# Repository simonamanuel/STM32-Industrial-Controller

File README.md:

# STM32 Industrial Sensor, DAQ & Actuator Controller

**Status: CAD-stage portfolio design (Revision D). Not fabricated, physically tested, or approved for industrial deployment.**

This repository contains an electronic design project built around an STM32F103C8T6 microcontroller, with a four-layer KiCad PCB, mixed-signal sensing, low-voltage power conversion, wired communications, and two switched DC actuator channels. It showcases design-file organization, schematic/PCB review, bill-of-materials management, and documented limitations.

## PCB Design Gallery

### PCB Layout

### 3D PCB View

### Front Copper Routing

### Electrical Schematic
[View Schematic PDF](KiCad/STM32_Industrial_Controller.pdf)

## At a glance

| Aspect | Revision D design target / supplied evidence |
| --- | --- |
| PCB | 4 layers, 218 × 146 mm, 1.6 mm FR-4 (per fabrication notes) |
| Controller | STM32F103C8T6, 3.3 V logic |
| Input | 9–30 V DC for logic; actuator supply specified separately as 9–18 V, nominal 12 V |
| Power rails | 5 V buck regulator, 3.3 V LDO |
| Analog sensing | Two nominal 0–10 V inputs with scaling/filtering to MCU ADC range |
| Interfaces | I²C, SPI, UART, SWD, half-duplex RS-485 |
| Actuators | Two nominal 1.5 A low-side switched channels (design target, not measured) |
| Schematic ERC | **0 errors / 0 warnings** in supplied Revision D report; four ERC check categories ignored |
| PCB DRC | **0 reported violations; 0 unconnected pads; 0 footprint errors**, none ignored in supplied report |
| Firmware | Not included in this Revision D archive; no firmware build or tests claimed |
| Physical verification | **Not performed** |

## System overview

```mermaid
flowchart TD
  A[External DC supply] --> B[Fuse + input protection]
  B --> C[Protected DC distribution]
  C --> D[5 V buck regulator]
  D --> E[3.3 V LDO]
  E --> F[STM32F103C8T6]
  G[Two analog sensor inputs] --> F
  F <--> H[I2C / SPI / UART / SWD]
  F <--> I[RS-485 transceiver]
  C --> J[Two fused actuator supplies]
  F --> K[Two MOSFET low-side switches]
  J --> K
```

The block diagram summarizes intended functions; it does not replace the authoritative schematic or prove electrical performance.

## Repository layout

- [`KiCad/`](KiCad/) — editable KiCad 10 schematic and four-layer PCB, project settings and local footprints.
- [`Manufacturing/`](Manufacturing/) — existing design-stage Gerbers, drills, BOM, placement outputs, ERC/DRC reports, and fabrication notes. **Not approved for production or ordering.**
- [`Documentation/DESIGN_SUMMARY.md`](Documentation/DESIGN_SUMMARY.md) — architecture and design assumptions.
- [`Documentation/VERIFICATION_STATUS.md`](Documentation/VERIFICATION_STATUS.md) — what has and has not been validated.
- [`Documentation/OPEN_DESIGN_ITEMS.md`](Documentation/OPEN_DESIGN_ITEMS.md) — unresolved concerns and disclosure statements.
- [`Documentation/PORTFOLIO_PRESENTATION.md`](Documentation/PORTFOLIO_PRESENTATION.md) — engineering scope, design deliverables, and verification status.
- [`Documentation/FINISHING_CHECKLIST.md`](Documentation/FINISHING_CHECKLIST.md) — minimal remaining steps for a CAD-only portfolio.
- [`Documentation/Original_Revision_D_README.md`](Documentation/Original_Revision_D_README.md) — README supplied with original Revision D archive, preserved unchanged.

## Opening the project

1. Open `KiCad/STM32_Industrial_Controller.kicad_pro` in KiCad 10 on macOS.
2. Open the `.kicad_sch` schematic and `.kicad_pcb` board.
3. Run **Inspect → Electrical Rules Checker** in Schematic Editor.
4. Run **Inspect → Design Rules Checker** in PCB Editor, enabling zone refill and schematic-parity checking.
5. Capture schematic, copper-layer, and KiCad 3D Viewer screenshots for the portfolio; see the finishing checklist.

## Engineering status and limitations

The **provided** ERC and DRC reports show clean CAD rule checks. Those checks do not establish functional electrical correctness, actual thermal performance, component suitability, assembly fit, or field reliability. An independent KiCad rerun was not performed during preparation of these portfolio documents.

**Known unresolved review item:** the design directly drives `IRLML0060` MOSFET gates from approximately 3.3 V MCU logic. Their guaranteed on-resistance is not specified at that exact gate voltage in the previously reviewed datasheet. The 1.5 A actuator performance at 3.3 V gate drive is therefore **not claimed as verified**. A separate gate-driver integration was proposed but was **not incorporated into this Revision D baseline**. Additional footprint/mechanical and continuous-current/thermal reviews remain open; see [`OPEN_DESIGN_ITEMS.md`](Documentation/OPEN_DESIGN_ITEMS.md).

**This design is not a safety controller, not a certified industrial product, and not a physical prototype.**

## Project objectives

This project explores the design and integration of embedded control hardware, mixed-signal sensor interfaces, industrial communication protocols, protected power distribution, and actuator-control circuitry.

Future development will focus on resolving outstanding electrical design considerations, PCB fabrication, hardware bring-up, embedded firmware development, and experimental performance verification.

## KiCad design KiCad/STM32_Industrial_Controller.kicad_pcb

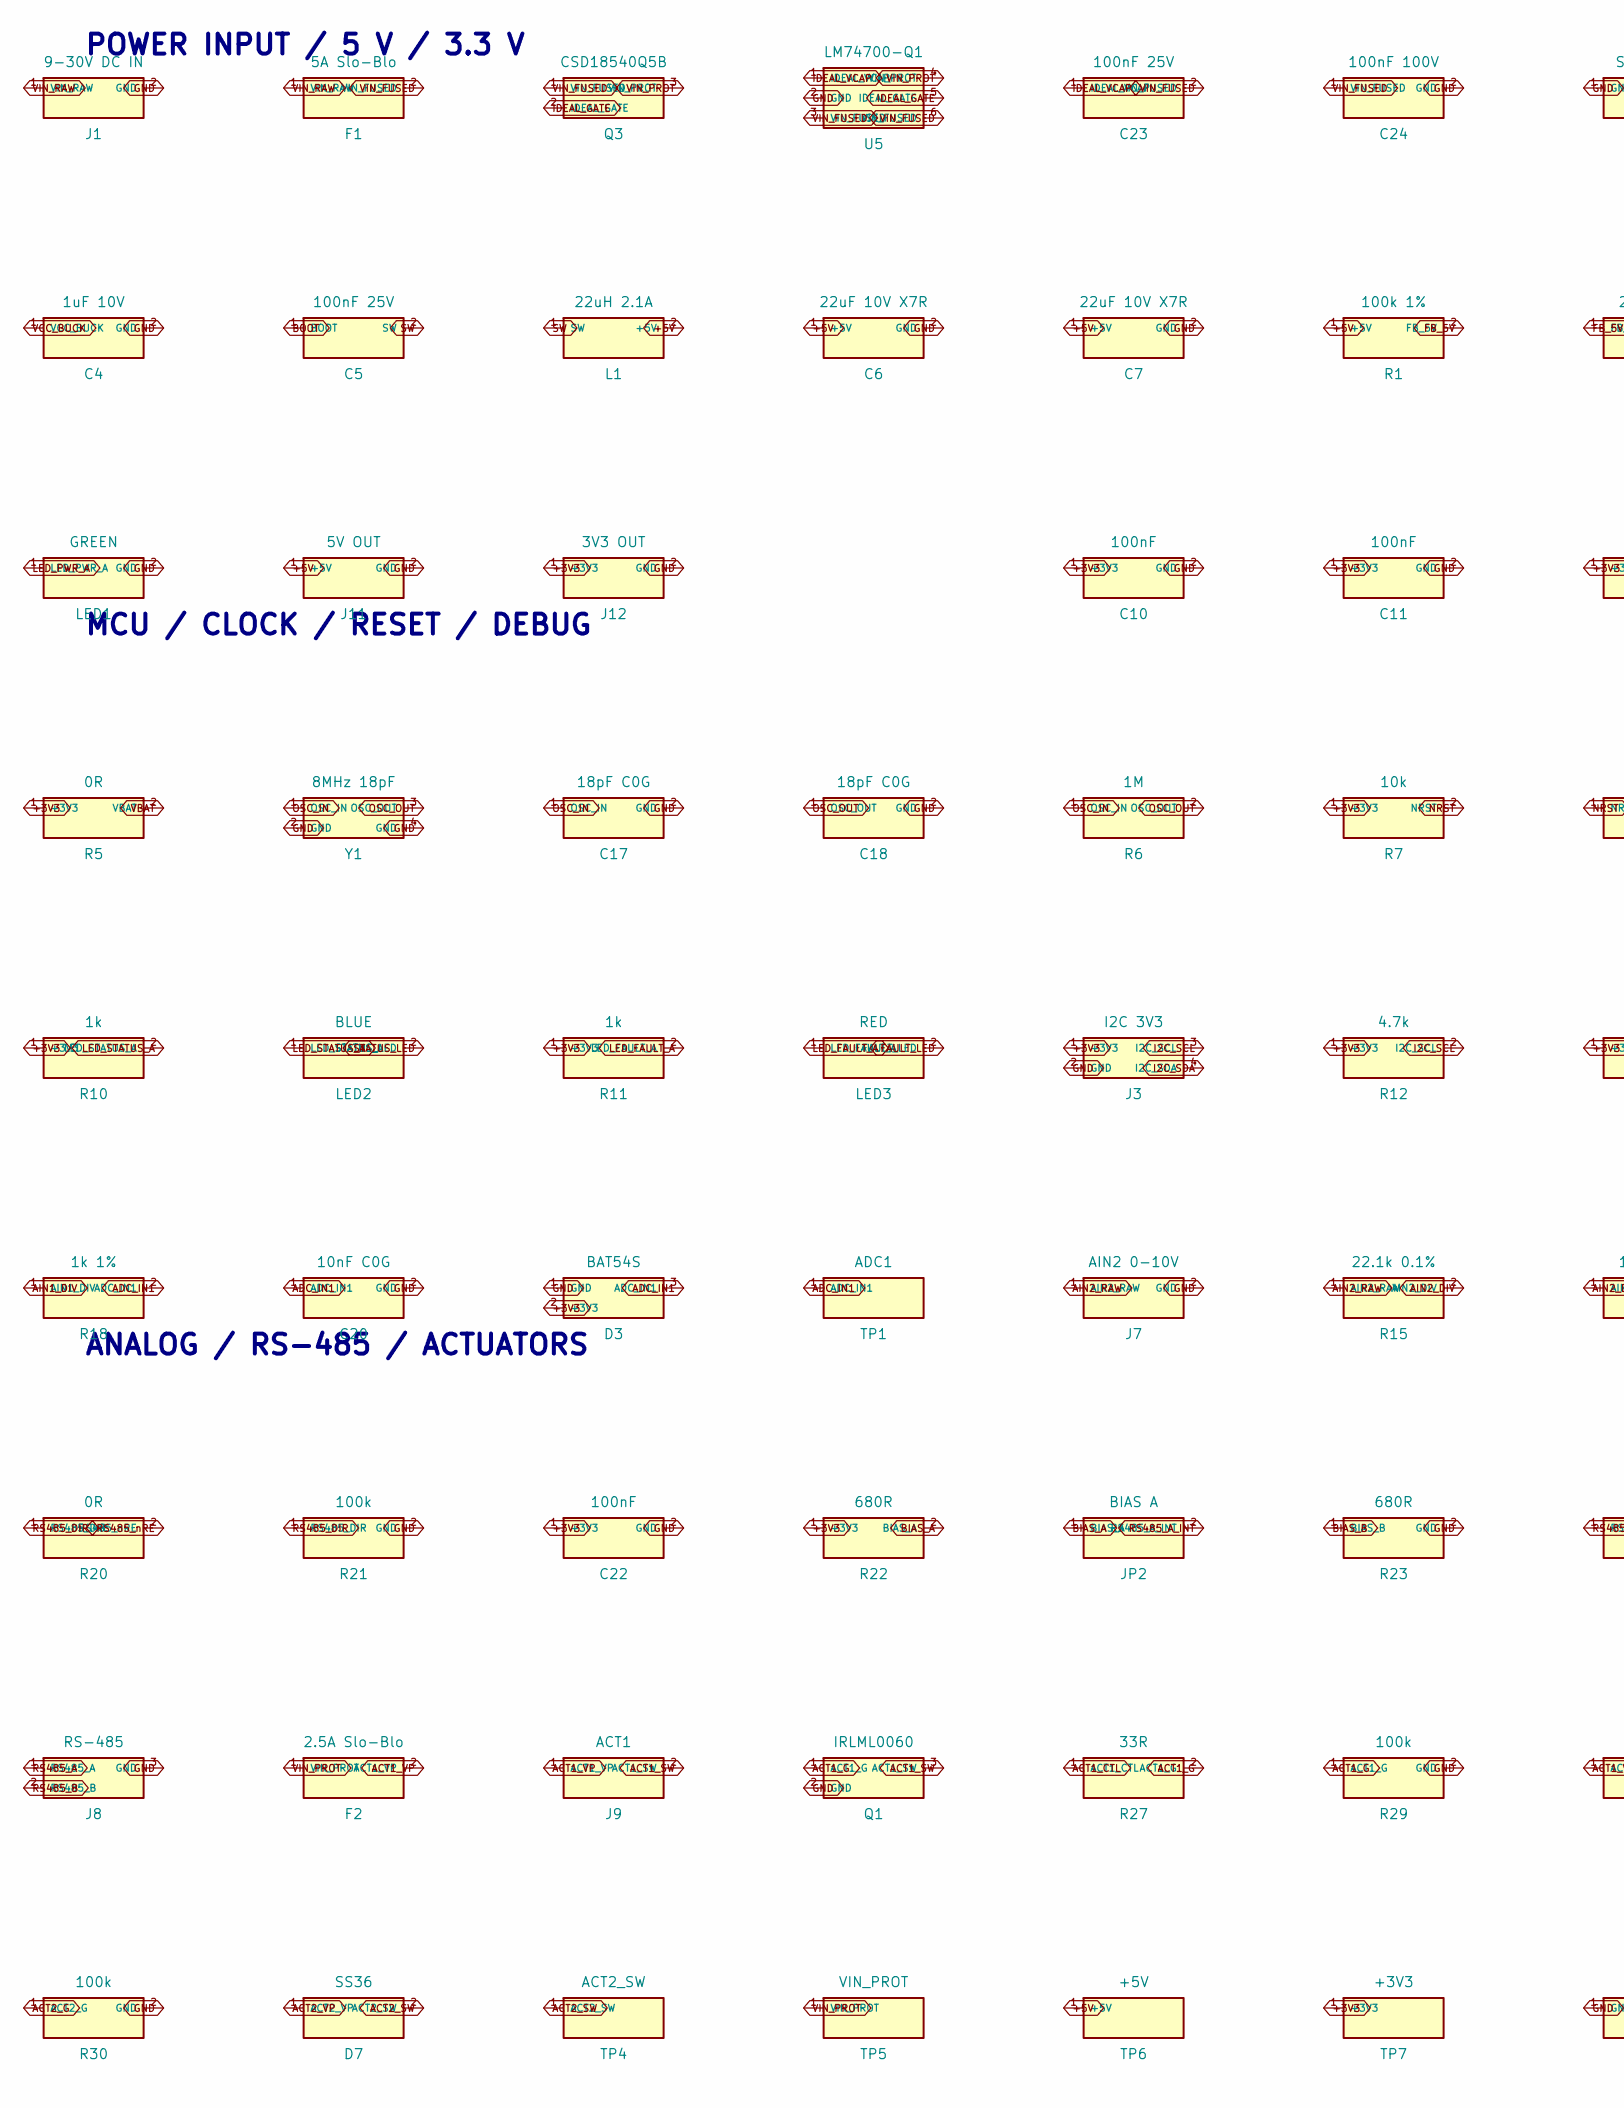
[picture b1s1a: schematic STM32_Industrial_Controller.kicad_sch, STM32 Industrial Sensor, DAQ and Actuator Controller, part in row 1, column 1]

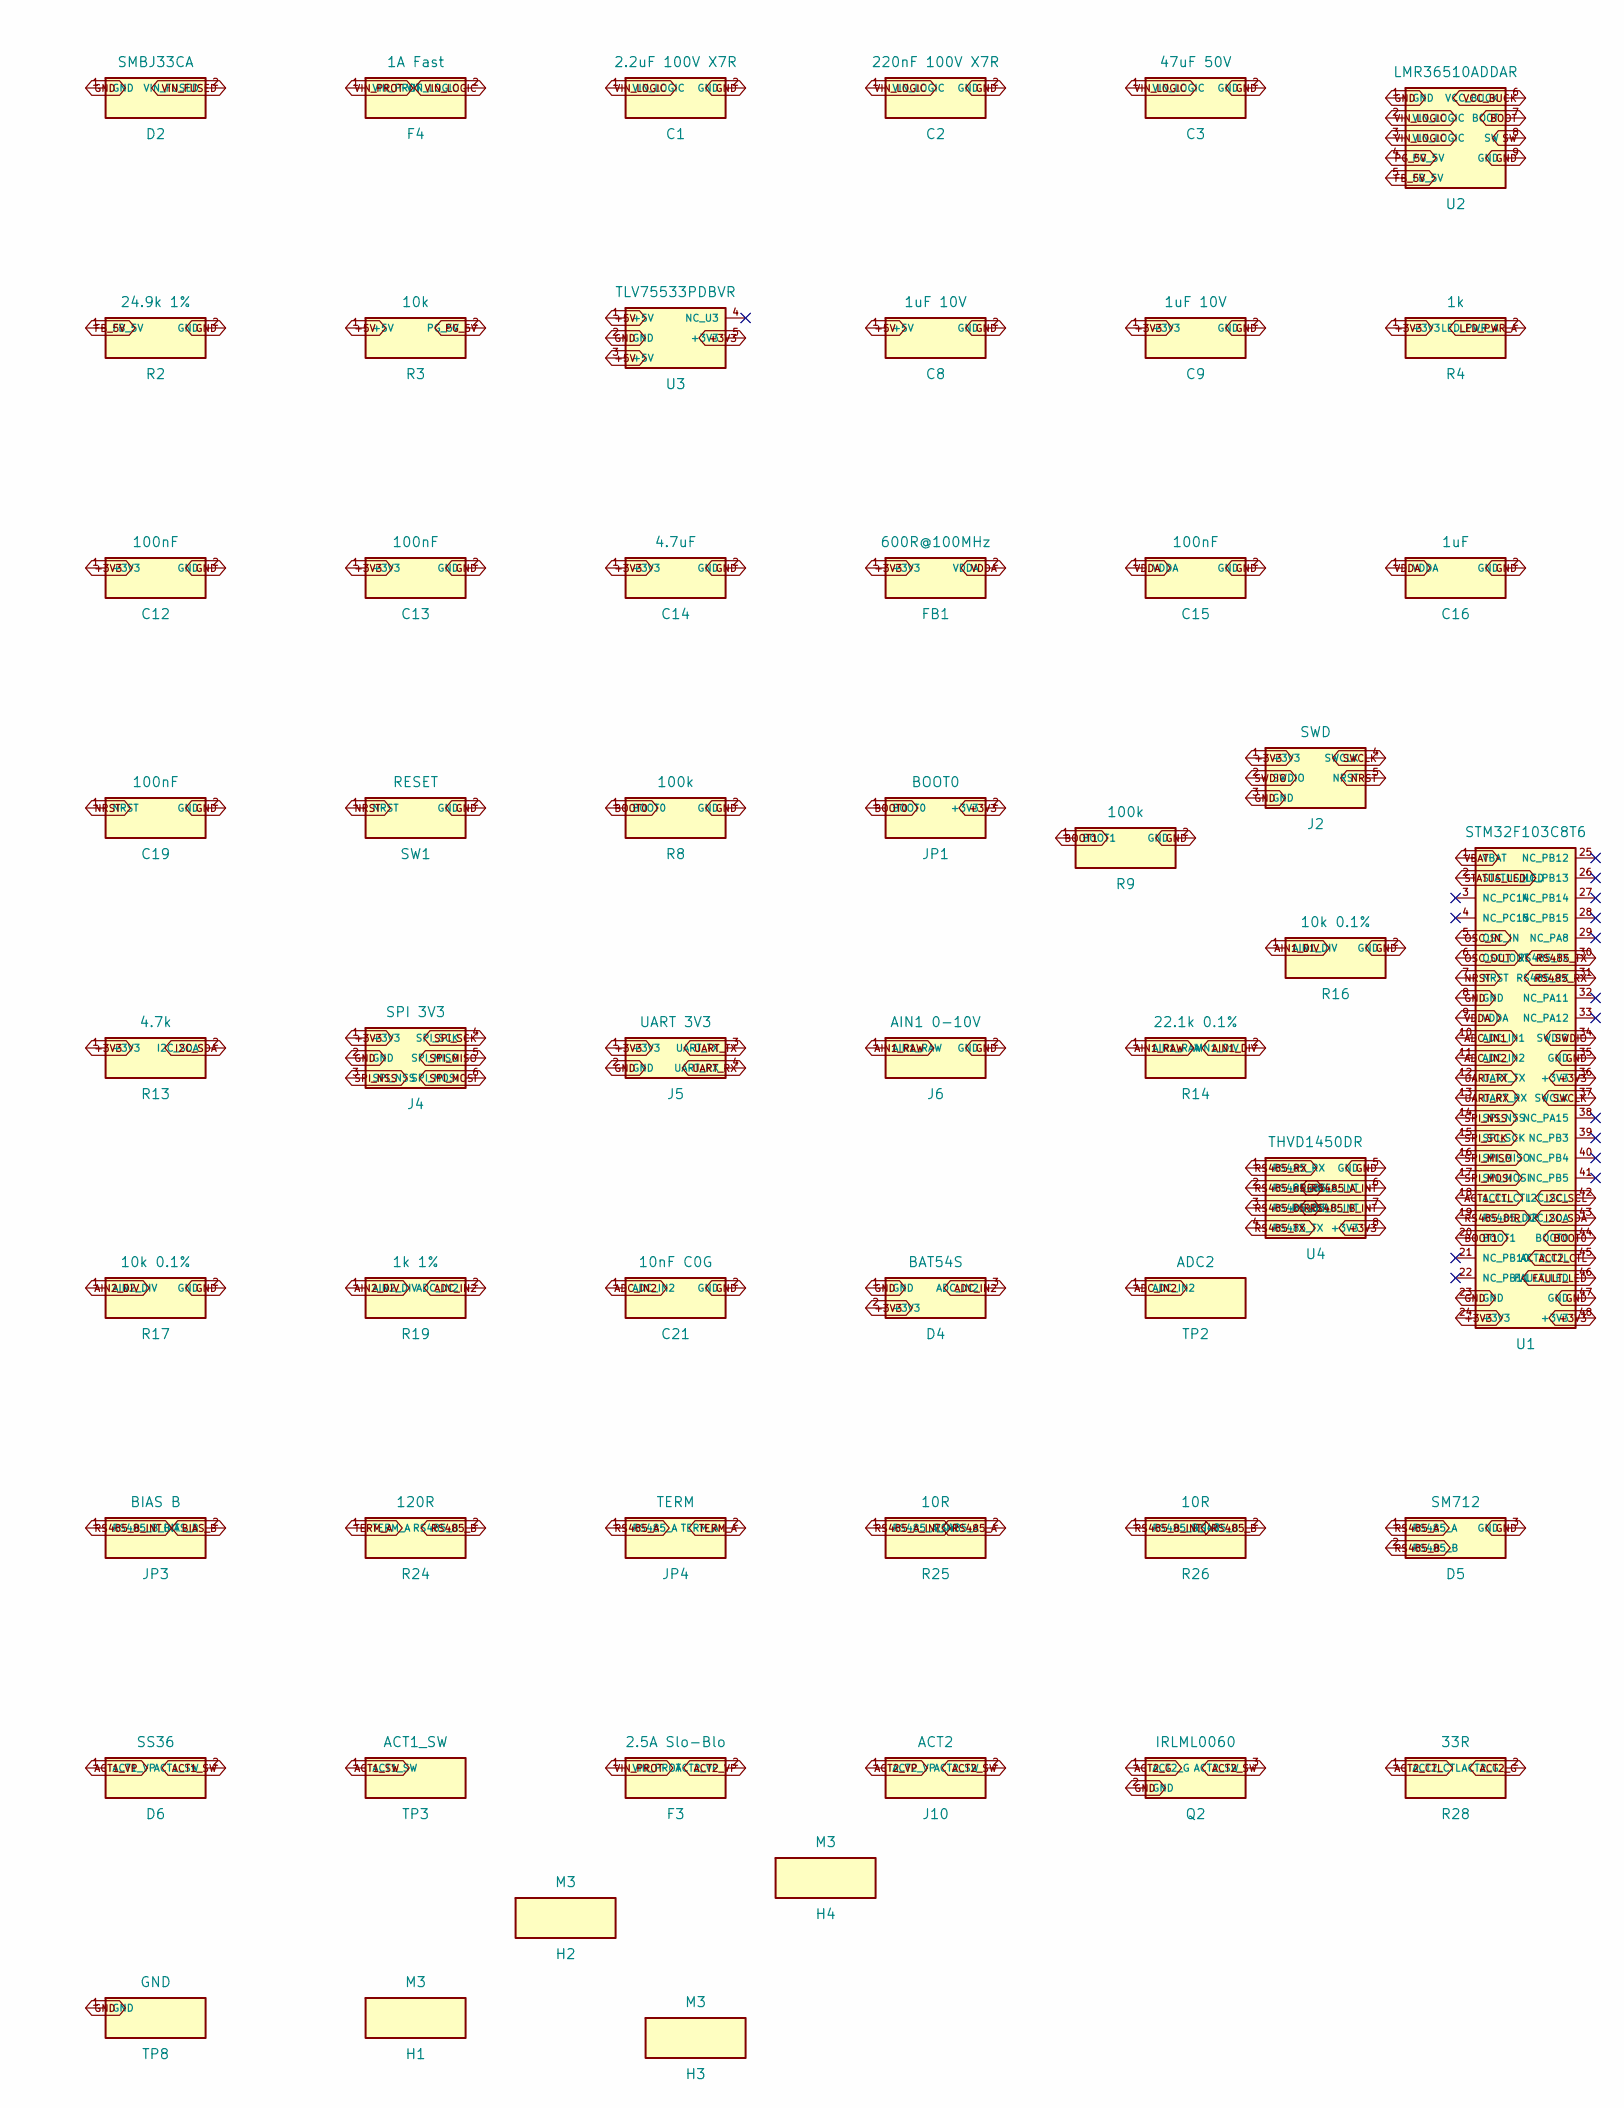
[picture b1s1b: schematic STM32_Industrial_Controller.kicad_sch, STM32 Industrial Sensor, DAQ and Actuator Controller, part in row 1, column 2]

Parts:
C1: 2.2uF 100V X7R; C1210
C2: 220nF 100V X7R; C0603
C3: 47uF 50V; CAP_SMD_63
C4, C8, C9: 1uF 10V; C0603
C5, C23: 100nF 25V; C0603
C6, C7: 22uF 10V X7R; C1210
C10, C11, C12, C13, C15, C19, C22: 100nF; C0603
C14: 4.7uF; C0603
C16: 1uF; C0603
C17, C18: 18pF C0G; C0603
C20, C21: 10nF C0G; C0603
C24: 100nF 100V; C0603
D2: SMBJ33CA; SMB
D3, D4: BAT54S; SOT23
D5: SM712; SOT23
D6, D7: SS36; SMA_K_RIGHT
F1: 5A Slo-Blo; FUSE_NANO2
F2, F3: 2.5A Slo-Blo; FUSE_NANO2
F4: 1A Fast; FUSE_NANO2
FB1: 600R@100MHz; R0603
H1, H2, H3, H4: M3; MOUNT
J1: 9-30V DC IN; TERM2
J2: SWD; HDR5
J3: I2C 3V3; HDR4
J4: SPI 3V3; HDR6
J5: UART 3V3; HDR4
J6: AIN1 0-10V; TERM2
J7: AIN2 0-10V; TERM2
J8: RS-485; TERM3
J9: ACT1; TERM2
J10: ACT2; TERM2
J11: 5V OUT; HDR2
J12: 3V3 OUT; HDR2
JP1: BOOT0; HDR2
JP2: BIAS A; HDR2
JP3: BIAS B; HDR2
JP4: TERM; HDR2
L1: 22uH 2.1A; IND_6X6
LED1: GREEN; LED0603
LED2: BLUE; LED0603
LED3: RED; LED0603
Q1, Q2: IRLML0060; SOT23
Q3: CSD18540Q5B; SON5X6_8
R1: 100k 1%; R0603
R2: 24.9k 1%; R0603
R3, R7: 10k; R0603
R4, R10, R11: 1k; R0603
R5, R20: 0R; R0603
R6: 1M; R0603
R8, R9, R21, R29, R30: 100k; R0603
R12, R13: 4.7k; R0603
R14, R15: 22.1k 0.1%; R0603
R16, R17: 10k 0.1%; R0603
R18, R19: 1k 1%; R0603
R22, R23: 680R; R0603
R24: 120R; R0603
R25, R26: 10R; R0603
R27, R28: 33R; R0603
SW1: RESET; BUTTON
TP1: ADC1; TP
TP2: ADC2; TP
TP3: ACT1_SW; TP
TP4: ACT2_SW; TP
TP5: VIN_PROT; TP
TP6: +5V; TP
TP7: +3V3; TP
TP8: GND; TP
U1: STM32F103C8T6; LQFP48
U2: LMR36510ADDAR; HSOIC8_EP
U3: TLV75533PDBVR; SOT23_5
U4: THVD1450DR; SOIC8
U5: LM74700-Q1; SOT23_6
Y1: 8MHz 18pF; XTAL4

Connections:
+3V3: C9.1 (+3V3), C10.1 (+3V3), C11.1 (+3V3), C12.1 (+3V3), C13.1 (+3V3), C14.1 (+3V3), C22.1 (+3V3), D3.2 (+3V3), D4.2 (+3V3), FB1.1 (+3V3), J2.1 (+3V3), J3.1 (+3V3), J4.1 (+3V3), J5.1 (+3V3), J12.1 (+3V3), JP1.2 (+3V3), R4.1 (+3V3), R5.1 (+3V3), R7.1 (+3V3), R10.1 (+3V3), R11.1 (+3V3), R12.1 (+3V3), R13.1 (+3V3), R22.1 (+3V3), TP7.1, U1.24 (+3V3), U1.36 (+3V3), U1.48 (+3V3), U3.5 (+3V3), U4.8 (+3V3)
+5V: C6.1 (+5V), C7.1 (+5V), C8.1 (+5V), J11.1 (+5V), L1.2 (+5V), R1.1 (+5V), R3.1 (+5V), TP6.1, U3.1 (+5V), U3.3 (+5V)
ACT1_CTL: R27.1 (ACT1_CTL), U1.18 (ACT1_CTL)
ACT1_G: Q1.1 (ACT1_G), R27.2 (ACT1_G), R29.1 (ACT1_G)
ACT1_SW: D6.2 (ACT1_SW), J9.2 (ACT1_SW), Q1.3 (ACT1_SW), TP3.1
ACT1_VP: D6.1 (ACT1_VP), F2.2 (ACT1_VP), J9.1 (ACT1_VP)
ACT2_CTL: R28.1 (ACT2_CTL), U1.45 (ACT2_CTL)
ACT2_G: Q2.1 (ACT2_G), R28.2 (ACT2_G), R30.1 (ACT2_G)
ACT2_SW: D7.2 (ACT2_SW), J10.2 (ACT2_SW), Q2.3 (ACT2_SW), TP4.1
ACT2_VP: D7.1 (ACT2_VP), F3.2 (ACT2_VP), J10.1 (ACT2_VP)
ADC_IN1: C20.1 (ADC_IN1), D3.3 (ADC_IN1), R18.2 (ADC_IN1), TP1.1, U1.10 (ADC_IN1)
ADC_IN2: C21.1 (ADC_IN2), D4.3 (ADC_IN2), R19.2 (ADC_IN2), TP2.1, U1.11 (ADC_IN2)
AIN1_DIV: R14.2 (AIN1_DIV), R16.1 (AIN1_DIV), R18.1 (AIN1_DIV)
AIN1_RAW: J6.1 (AIN1_RAW), R14.1 (AIN1_RAW)
AIN2_DIV: R15.2 (AIN2_DIV), R17.1 (AIN2_DIV), R19.1 (AIN2_DIV)
AIN2_RAW: J7.1 (AIN2_RAW), R15.1 (AIN2_RAW)
BIAS_A: JP2.1 (BIAS_A), R22.2 (BIAS_A)
BIAS_B: JP3.2 (BIAS_B), R23.1 (BIAS_B)
BOOT: C5.1 (BOOT), U2.7 (BOOT)
BOOT0: JP1.1 (BOOT0), R8.1 (BOOT0), U1.44 (BOOT0)
BOOT1: R9.1 (BOOT1), U1.20 (BOOT1)
FAULT_LED: LED3.2 (FAULT_LED), U1.46 (FAULT_LED)
FB_5V: R1.2 (FB_5V), R2.1 (FB_5V), U2.5 (FB_5V)
GND: C1.2 (GND), C2.2 (GND), C3.2 (GND), C4.2 (GND), C6.2 (GND), C7.2 (GND), C8.2 (GND), C9.2 (GND), C10.2 (GND), C11.2 (GND), C12.2 (GND), C13.2 (GND), C14.2 (GND), C15.2 (GND), C16.2 (GND), C17.2 (GND), C18.2 (GND), C19.2 (GND), C20.2 (GND), C21.2 (GND), C22.2 (GND), C24.2 (GND), D2.1 (GND), D3.1 (GND), D4.1 (GND), D5.3 (GND), J1.2 (GND), J2.3 (GND), J3.2 (GND), J4.2 (GND), J5.2 (GND), J6.2 (GND), J7.2 (GND), J8.3 (GND), J11.2 (GND), J12.2 (GND), LED1.2 (GND), Q1.2 (GND), Q2.2 (GND), R2.2 (GND), R8.2 (GND), R9.2 (GND), R16.2 (GND), R17.2 (GND), R21.2 (GND), R23.2 (GND), R29.2 (GND), R30.2 (GND), SW1.2 (GND), TP8.1, U1.8 (GND), U1.23 (GND), U1.35 (GND), U1.47 (GND), U2.1 (GND), U2.9 (GND), U3.2 (GND), U4.5 (GND), U5.2 (GND), Y1.2 (GND), Y1.4 (GND)
I2C_SCL: J3.3 (I2C_SCL), R12.2 (I2C_SCL), U1.42 (I2C_SCL)
I2C_SDA: J3.4 (I2C_SDA), R13.2 (I2C_SDA), U1.43 (I2C_SDA)
IDEAL_GATE: Q3.2 (IDEAL_GATE), U5.5 (IDEAL_GATE)
IDEAL_VCAP: C23.1 (IDEAL_VCAP), U5.1 (IDEAL_VCAP)
LED_FAULT_A: LED3.1 (LED_FAULT_A), R11.2 (LED_FAULT_A)
LED_PWR_A: LED1.1 (LED_PWR_A), R4.2 (LED_PWR_A)
LED_STATUS_A: LED2.1 (LED_STATUS_A), R10.2 (LED_STATUS_A)
NRST: C19.1 (NRST), J2.5 (NRST), R7.2 (NRST), SW1.1 (NRST), U1.7 (NRST)
OSC_IN: C17.1 (OSC_IN), R6.1 (OSC_IN), U1.5 (OSC_IN), Y1.1 (OSC_IN)
OSC_OUT: C18.1 (OSC_OUT), R6.2 (OSC_OUT), U1.6 (OSC_OUT), Y1.3 (OSC_OUT)
PG_5V: R3.2 (PG_5V), U2.4 (PG_5V)
RS485_A: D5.1 (RS485_A), J8.1 (RS485_A), JP4.1 (RS485_A), R25.2 (RS485_A)
RS485_A_INT: JP2.2 (RS485_A_INT), R25.1 (RS485_A_INT), U4.6 (RS485_A_INT)
RS485_B: D5.2 (RS485_B), J8.2 (RS485_B), R24.2 (RS485_B), R26.2 (RS485_B)
RS485_B_INT: JP3.1 (RS485_B_INT), R26.1 (RS485_B_INT), U4.7 (RS485_B_INT)
RS485_DIR: R20.1 (RS485_DIR), R21.1 (RS485_DIR), U1.19 (RS485_DIR), U4.3 (RS485_DIR)
RS485_RX: U1.31 (RS485_RX), U4.1 (RS485_RX)
RS485_TX: U1.30 (RS485_TX), U4.4 (RS485_TX)
RS485_nRE: R20.2 (RS485_nRE), U4.2 (RS485_nRE)
SPI_MISO: J4.5 (SPI_MISO), U1.16 (SPI_MISO)
SPI_MOSI: J4.6 (SPI_MOSI), U1.17 (SPI_MOSI)
SPI_NSS: J4.3 (SPI_NSS), U1.14 (SPI_NSS)
SPI_SCK: J4.4 (SPI_SCK), U1.15 (SPI_SCK)
STATUS_LED: LED2.2 (STATUS_LED), U1.2 (STATUS_LED)
SW: C5.2 (SW), L1.1 (SW), U2.8 (SW)
SWCLK: J2.4 (SWCLK), U1.37 (SWCLK)
SWDIO: J2.2 (SWDIO), U1.34 (SWDIO)
TERM_A: JP4.2 (TERM_A), R24.1 (TERM_A)
UART_RX: J5.4 (UART_RX), U1.13 (UART_RX)
UART_TX: J5.3 (UART_TX), U1.12 (UART_TX)
VBAT: R5.2 (VBAT), U1.1 (VBAT)
VCC_BUCK: C4.1 (VCC_BUCK), U2.6 (VCC_BUCK)
VDDA: C15.1 (VDDA), C16.1 (VDDA), FB1.2 (VDDA), U1.9 (VDDA)
VIN_FUSED: C23.2 (VIN_FUSED), C24.1 (VIN_FUSED), D2.2 (VIN_FUSED), F1.2 (VIN_FUSED), Q3.1 (VIN_FUSED), U5.3 (VIN_FUSED), U5.6 (VIN_FUSED)
VIN_LOGIC: C1.1 (VIN_LOGIC), C2.1 (VIN_LOGIC), C3.1 (VIN_LOGIC), F4.2 (VIN_LOGIC), U2.2 (VIN_LOGIC), U2.3 (VIN_LOGIC)
VIN_PROT: F2.1 (VIN_PROT), F3.1 (VIN_PROT), F4.1 (VIN_PROT), Q3.3 (VIN_PROT), TP5.1, U5.4 (VIN_PROT)
VIN_RAW: F1.1 (VIN_RAW), J1.1 (VIN_RAW)

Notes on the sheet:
ANALOG / RS-485 / ACTUATORS
POWER INPUT / 5 V / 3.3 V
MCU / CLOCK / RESET / DEBUG

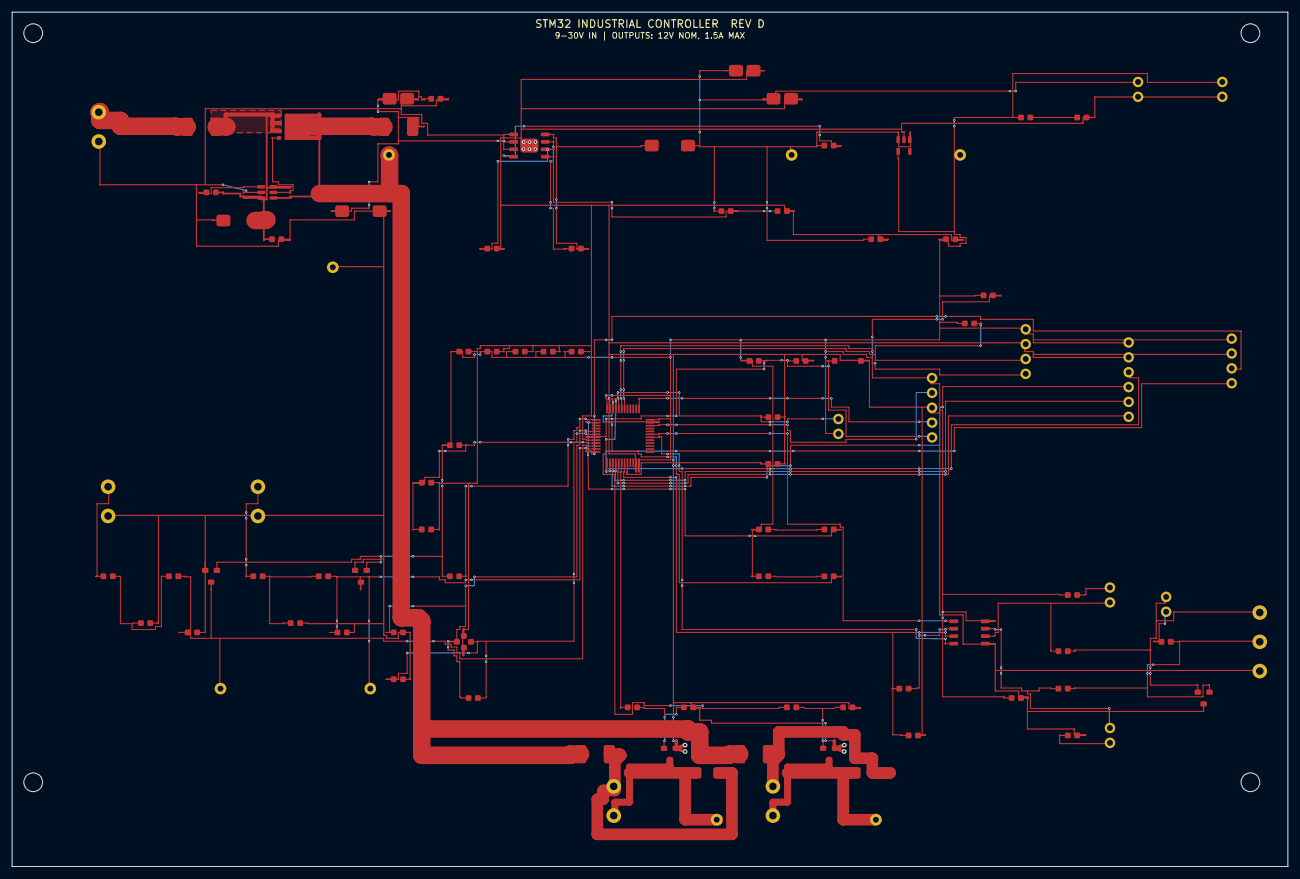
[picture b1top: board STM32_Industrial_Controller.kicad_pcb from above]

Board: 4 copper layers, 218.0 x 146.0 mm, 107 parts (0 on the bottom side), 61 nets.

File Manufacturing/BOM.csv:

Reference,Quantity,Value,Manufacturer Part Number,Footprint,Description,Populate
C1,1,2.2uF 100V X7R,GRM32ER72A225KA35L,C1210,Buck input capacitor,YES
C10 C11 C12 C13,4,100nF,GRM188R71C104KA01D,C0603,MCU local decoupling,YES
C14,1,4.7uF,GRM188R71A475KE15D,C0603,MCU bulk decoupling,YES
C15,1,100nF,GRM188R71C104KA01D,C0603,VDDA bypass,YES
C16,1,1uF,GRM188R71A105KA61D,C0603,VDDA reservoir,YES
C17 C18,2,18pF C0G,GRM1885C1H180JA01D,C0603,Crystal load,YES
C19,1,100nF,GRM188R71C104KA01D,C0603,Reset filter,YES
C2,1,220nF 100V X7R,CGA4J3X7S2A224K125AB,C0603,High-frequency input bypass,YES
C20 C21,2,10nF C0G,GRM1885C1H103JA01D,C0603,ADC anti-alias filter,YES
C22,1,100nF,GRM188R71C104KA01D,C0603,RS-485 decoupling,YES
C23,1,100nF 25V,GRM188R71E104KA01D,C0603,Ideal-diode charge-pump capacitor,YES
C24,1,100nF 100V,CGA3E2X7R2A104K080AA,C0603,Ideal-diode input bypass,YES
C3,1,47uF 50V,EEE-FK1H470P,CAP_SMD_63,Logic-branch input bulk capacitor,YES
C4,1,1uF 10V,GRM188R71A105KA61D,C0603,Buck VCC bypass,YES
C5,1,100nF 25V,GRM188R71E104KA01D,C0603,Bootstrap capacitor,YES
C6 C7,2,22uF 10V X7R,GRM32ER71A226KE20L,C1210,5 V output capacitor,YES
C8,1,1uF 10V,GRM188R71A105KA61D,C0603,LDO input capacitor,YES
C9,1,1uF 10V,GRM188R71A105KA61D,C0603,LDO output capacitor,YES
D2,1,SMBJ33CA,SMBJ33CA-13-F,SMB,Bidirectional input transient suppressor,YES
D3 D4,2,BAT54S,BAT54S-7-F,SOT23,ADC Schottky rail clamp,YES
D5,1,SM712,SM712-02HTG,SOT23,RS-485 asymmetric TVS,YES
D6 D7,2,SS36,SS36,SMA_K_RIGHT,60 V inductive flyback diode,YES
F1,1,5A Slo-Blo,Littelfuse 0454005.MR,FUSE_NANO2,125 V time-delay main input fuse,YES
F2 F3,2,2.5A Slo-Blo,Littelfuse 045402.5MR,FUSE_NANO2,125 V time-delay actuator fuse,YES
F4,1,1A Fast,Littelfuse 0451001.MRL,FUSE_NANO2,125 V logic-branch fuse,YES
FB1,1,600R@100MHz,BLM18AG601SN1D,R0603,Analog supply ferrite,YES
J1,1,9-30V DC IN,Phoenix 1935161,TERM2,5.00 mm input terminal,YES
J10,1,ACT2,Phoenix 1935161,TERM2,5.00 mm actuator terminal,YES
J11,1,5V OUT,M20-9990246,HDR2,Limited auxiliary 5 V header,YES
J12,1,3V3 OUT,M20-9990246,HDR2,Limited auxiliary 3.3 V header,YES
J2,1,SWD,M20-9980546,HDR5,SWD programming header,YES
J3,1,I2C 3V3,M20-9990446,HDR4,I2C connector,YES
J4,1,SPI 3V3,M20-9980646,HDR6,SPI connector,YES
J5,1,UART 3V3,M20-9990446,HDR4,UART connector,YES
J6,1,AIN1 0-10V,Phoenix 1935161,TERM2,5.00 mm analog input terminal,YES
J7,1,AIN2 0-10V,Phoenix 1935161,TERM2,5.00 mm analog input terminal,YES
J8,1,RS-485,Phoenix 1935174,TERM3,RS-485 terminal,YES
J9,1,ACT1,Phoenix 1935161,TERM2,5.00 mm actuator terminal,YES
JP1,1,BOOT0,M20-9990246,HDR2,Bootloader selection jumper,YES
JP2,1,BIAS A,M20-9990246,HDR2,Failsafe bias enable,YES
JP3,1,BIAS B,M20-9990246,HDR2,Failsafe bias enable,YES
JP4,1,TERM,M20-9990246,HDR2,Termination enable,YES
L1,1,22uH 2.1A,SRN6045TA-220M,IND_6X6,Buck inductor,YES
LED1,1,GREEN,LTST-C190KGKT,LED0603,3.3 V power indicator,YES
LED2,1,BLUE,LTST-C190TBKT,LED0603,Active-low status LED,YES
LED3,1,RED,LTST-C190KRKT,LED0603,Active-low fault LED,YES
Q1 Q2,2,IRLML0060,IRLML0060TRPBF,SOT23,60 V logic-level actuator NMOS,YES
Q3,1,CSD18540Q5B,CSD18540Q5B,SON5X6_8,60 V 2.2 mOhm ideal-diode MOSFET,YES
R1,1,100k 1%,RC0603FR-07100KL,R0603,Buck feedback top,YES
R10,1,1k,RC0603FR-071KL,R0603,Status LED resistor,YES
R11,1,1k,RC0603FR-071KL,R0603,Fault LED resistor,YES
R12 R13,2,4.7k,RC0603FR-074K7L,R0603,I2C pull-up,YES
R14 R15,2,22.1k 0.1%,ERA-3AEB2212V,R0603,Analog divider top,YES
R16 R17,2,10k 0.1%,ERA-3AEB103V,R0603,Analog divider bottom,YES
R18 R19,2,1k 1%,RC0603FR-071KL,R0603,ADC isolation/filter resistor,YES
R2,1,24.9k 1%,RC0603FR-0724K9L,R0603,Buck feedback bottom,YES
R20,1,0R,RC0603JR-070RL,R0603,Couples driver and receiver direction,YES
R21,1,100k,RC0603FR-07100KL,R0603,RS-485 reset-safe receive default,YES
R22,1,680R,RC0603FR-07680RL,R0603,Optional failsafe pull-up,YES
R23,1,680R,RC0603FR-07680RL,R0603,Optional failsafe pull-down,YES
R24,1,120R,RC0603FR-07120RL,R0603,RS-485 termination,YES
R25 R26,2,10R,RC0603FR-0710RL,R0603,Bus damping,YES
R27 R28,2,33R,RC0603FR-0733RL,R0603,MOSFET gate resistor,YES
R29 R30,2,100k,RC0603FR-07100KL,R0603,MOSFET reset-state pull-down,YES
R3,1,10k,RC0603FR-0710KL,R0603,Power-good pull-up,YES
R4,1,1k,RC0603FR-071KL,R0603,Power LED resistor,YES
R5,1,0R,RC0603JR-070RL,R0603,VBAT supply link,YES
R6,1,1M,RC0603FR-071ML,R0603,Crystal bias resistor,YES
R7,1,10k,RC0603FR-0710KL,R0603,Reset pull-up,YES
R8,1,100k,RC0603FR-07100KL,R0603,BOOT0 default low,YES
R9,1,100k,RC0603FR-07100KL,R0603,BOOT1 default low,YES
SW1,1,RESET,B3U-1000P,BUTTON,Reset pushbutton,YES
TP1,1,ADC1,5015,TP,ADC test point,YES
TP2,1,ADC2,5015,TP,ADC test point,YES
TP3,1,ACT1_SW,5015,TP,Output test point,YES
TP4,1,ACT2_SW,5015,TP,Output test point,YES
TP5,1,VIN_PROT,5015,TP,Power rail test point,YES
TP6,1,+5V,5015,TP,Power rail test point,YES
TP7,1,+3V3,5015,TP,Power rail test point,YES
TP8,1,GND,5015,TP,Power rail test point,YES
U1,1,STM32F103C8T6,STM32F103C8T6,LQFP48,72 MHz Arm Cortex-M3 MCU,YES
U2,1,LMR36510ADDAR,LMR36510ADDAR,HSOIC8_EP,"65 V, 1 A synchronous buck",YES
U3,1,TLV75533PDBVR,TLV75533PDBVR,SOT23_5,500 mA 3.3 V LDO,YES
U4,1,THVD1450DR,THVD1450DR,SOIC8,3.3 V half-duplex RS-485,YES
U5,1,LM74700-Q1,LM74700QDBVRQ1,SOT23_6,65 V ideal-diode/reverse-polarity controller,YES
Y1,1,8MHz 18pF,NX3225GD-8MHZ-STD-CRA-3,XTAL4,Main crystal,YES

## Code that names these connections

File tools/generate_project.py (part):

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add("JP3", "BIAS B", "M20-9990246", "HDR2", {1:"RS485_B_INT",2:"BIAS_B"}, 120,80,"Failsafe bias enable")
add("R24", "120R", "RC0603FR-07120RL", "R0603", {1:"TERM_A",2:"RS485_B"}, 126,70,"RS-485 termination")
add("JP4", "TERM", "M20-9990246", "HDR2", {1:"RS485_A",2:"TERM_A"}, 126,66,"Termination enable")
add("R25", "10R", "RC0603FR-0710RL", "R0603", {1:"RS485_A_INT",2:"RS485_A"}, 115,71,"Bus damping")
add("R26", "10R", "RC0603FR-0710RL", "R0603", {1:"RS485_B_INT",2:"RS485_B"}, 115,75,"Bus damping")
add("D5", "SM712", "SM712-02HTG", "SOT23", {1:"RS485_A",2:"RS485_B",3:"GND"}, 130,76,"RS-485 asymmetric TVS")
add("J8", "RS-485", "Phoenix 1935174", "TERM3", {1:"RS485_A",2:"RS485_B",3:"GND"}, 136,70,"RS-485 terminal")

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        pinname={10:"PA0",11:"PA1",12:"PA2",13:"PA3",14:"PA4",15:"PA5",16:"PA6",17:"PA7",18:"PB0",19:"PB1",20:"PB2",30:"PA9",31:"PA10",34:"PA13",37:"PA14",42:"PB6",43:"PB7",44:"BOOT0",45:"PB8",46:"PB9",2:"PC13"}
        for pin,net in mcu.items():
            if net in fn: w.writerow([pin,pinname.get(pin,""),net,fn[net],"Low/output disabled" if "ACT" in net or net=="RS485_DIR" else "Input/Hi-Z until configured"])
    def netclass(name,width,via,drill):
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    classes=[netclass("Default",.15,.40,.20),netclass("Power Main",3.0,.80,.40),netclass("Power Channel",2.0,.80,.40),netclass("Power Logic",.20,.60,.30),netclass("Ground",.20,.80,.40)]
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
